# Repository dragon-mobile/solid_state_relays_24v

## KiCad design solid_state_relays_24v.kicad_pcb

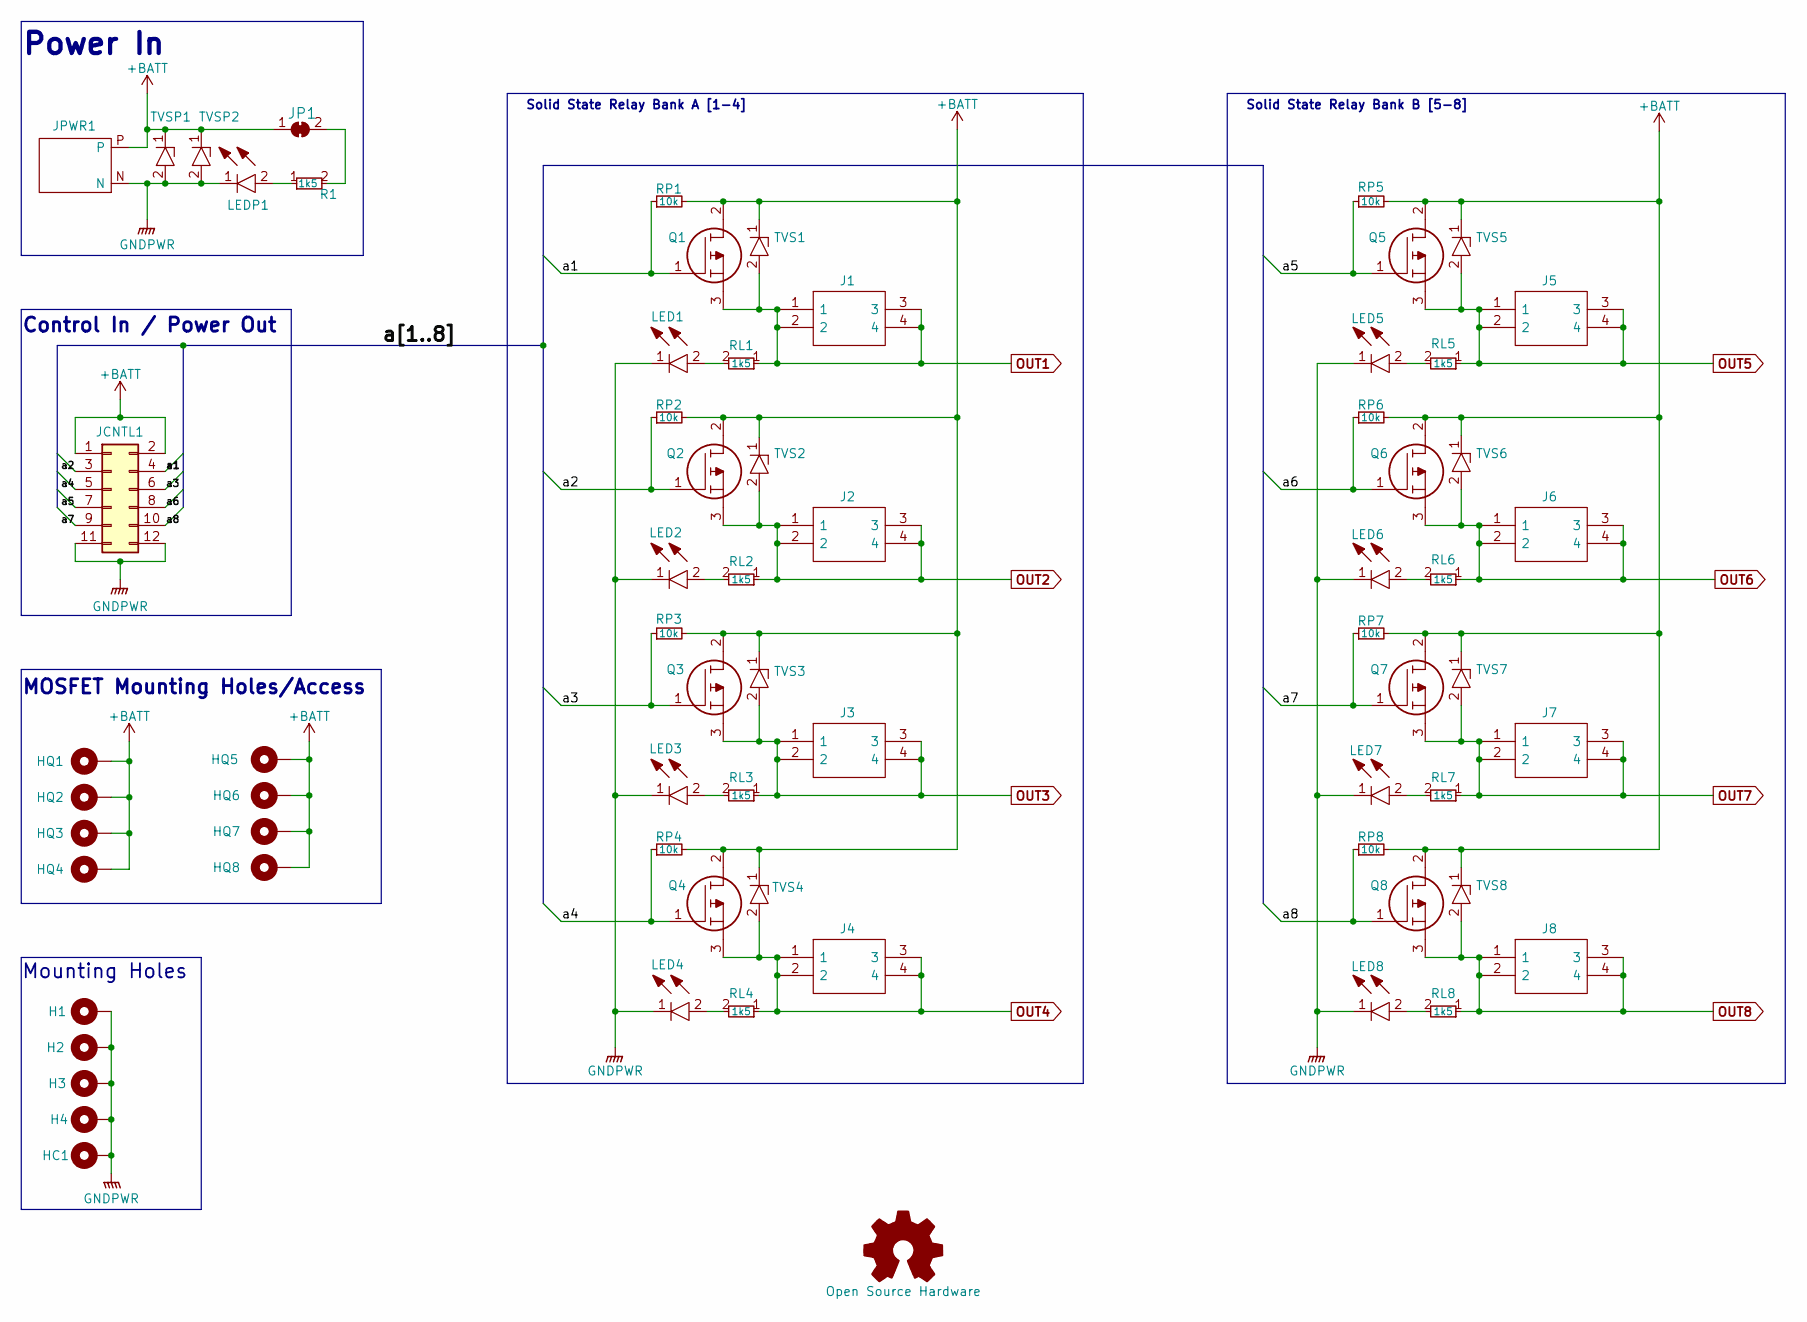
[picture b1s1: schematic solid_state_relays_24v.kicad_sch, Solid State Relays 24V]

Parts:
H1, H2, H3, H4: MountingHole; MountingHole_3.2mm_M3_Pad_Via
HC1: MountingHole; MountingHole_3.2mm_M3_Pad_Via
HQ1, HQ2, HQ3, HQ4, HQ5, HQ6, HQ7, HQ8: HeatsinkHole; MountingHole_3.2mm_M3_Pad_Via
J1, J2, J3, J4, J5, J6, J7, J8: 1190297; Mouser Part Number 651-1190297
JCNTL1: Conn_02x06_Odd_Even; IDC-Header_2x06_P2.54mm_Horizontal; MPN 78207-1012HLF; Mouser Part Number 649-78207-112HLF
JP1: SolderJumper_2_Bridged; SolderJumper-2_P1.3mm_Bridged_RoundedPad1.0x1.5mm
JPWR1: XT60PW-M; XT60PWM; Manufacturer_Part_Number XT60PW-M
LED1, LED2, LED3, LED4, LED5, LED6, LED7, LED8: LTST-C190KFKT; LEDC1607X80N; Mouser Part Number 859-LTST-C190KFKT
LEDP1: LTST-C190KGKT; LEDC1608X80N; Mouser Part Number 859-LTST-C190KGKT
Q1, Q2, Q3, Q4, Q5, Q6, Q7, Q8: IRF4905PBF; TO254P469X1042X1967-3P; Mouser Part Number 942-IRF4905PBF
R1: 1k5; RESC2012X65N; Manufacturer_Part_Number SDR10EZPJ152; Mouser Part Number 755-SDR10EZPJ152
RL1, RL2, RL3, RL4, RL5, RL6, RL7, RL8: 1k5; RESC2012X65N; Manufacturer_Part_Number SDR10EZPJ152; Mouser Part Number 755-SDR10EZPJ152
RP1, RP2, RP3, RP4, RP5, RP6, RP7, RP8: 10k; RESC2012X65N
TVS1, TVS2, TVS3, TVS4, TVS5, TVS6, TVS7, TVS8: SM6T30AY; SMBJ36CATR; Mouser Part Number 511-SM6T30AY
TVSP1, TVSP2: SM6T30AY; SMBJ36CATR; Mouser Part Number 511-SM6T30AY

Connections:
+BATT: HQ1.1, HQ2.1, HQ3.1, HQ4.1, HQ5.1, HQ6.1, HQ7.1, HQ8.1, JCNTL1.1, JCNTL1.2, JP1.1 (A), JPWR1.P, Q1.2, Q2.2, Q3.2, Q4.2, Q5.2, Q6.2, Q7.2, Q8.2, RP1.2, RP2.2, RP3.2, RP4.2, RP5.2, RP6.2, RP7.2, RP8.2, TVS1.1, TVS2.1, TVS3.1, TVS4.1, TVS5.1, TVS6.1, TVS7.1, TVS8.1, TVSP1.1, TVSP2.1
/a1: JCNTL1.4, Q1.1, RP1.1
/a2: JCNTL1.3, Q2.1, RP2.1
/a3: JCNTL1.6, Q3.1, RP3.1
/a4: JCNTL1.5, Q4.1, RP4.1
/a5: JCNTL1.7, Q5.1, RP5.1
/a6: JCNTL1.8, Q6.1, RP6.1
/a7: JCNTL1.9, Q7.1, RP7.1
/a8: JCNTL1.10, Q8.1, RP8.1
GNDPWR: H1.1, H2.1, H3.1, H4.1, HC1.1, JCNTL1.11, JCNTL1.12, JPWR1.N, LED1.1, LED2.1, LED3.1, LED4.1, LED5.1, LED6.1, LED7.1, LED8.1, LEDP1.1, TVSP1.2, TVSP2.2
unnamed: JP1.2 (B), R1.2
unnamed: LED1.2, RL1.2
unnamed: LED2.2, RL2.2
unnamed: LED3.2, RL3.2
unnamed: LED4.2, RL4.2
unnamed: LED5.2, RL5.2
unnamed: LED6.2, RL6.2
unnamed: LED7.2, RL7.2
unnamed: LED8.2, RL8.2
unnamed: LEDP1.2, R1.1
OUT1: J1.1, J1.2, J1.3, J1.4, Q1.3, RL1.1, TVS1.2
OUT2: J2.1, J2.2, J2.3, J2.4, Q2.3, RL2.1, TVS2.2
OUT3: J3.1, J3.2, J3.3, J3.4, Q3.3, RL3.1, TVS3.2
OUT4: J4.1, J4.2, J4.3, J4.4, Q4.3, RL4.1, TVS4.2
OUT5: J5.1, J5.2, J5.3, J5.4, Q5.3, RL5.1, TVS5.2
OUT6: J6.1, J6.2, J6.3, J6.4, Q6.3, RL6.1, TVS6.2
OUT7: J7.1, J7.2, J7.3, J7.4, Q7.3, RL7.1, TVS7.2
OUT8: J8.1, J8.2, J8.3, J8.4, Q8.3, RL8.1, TVS8.2

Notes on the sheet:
Control In / Power Out
Mounting Holes
MOSFET Mounting Holes/Access
Solid State Relay Bank B [5-8]
Solid State Relay Bank A [1-4]
Power In

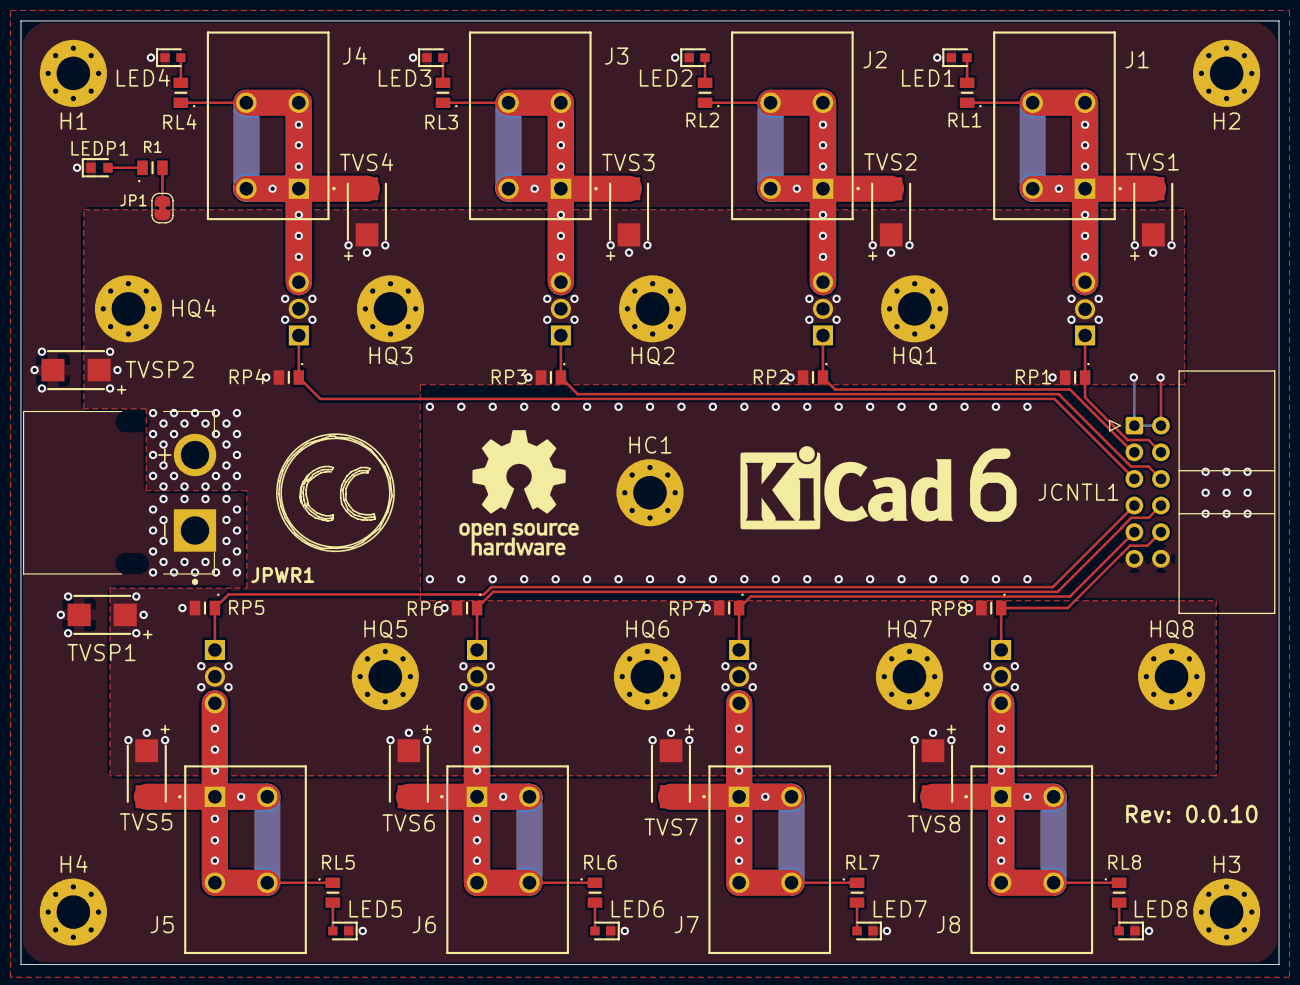
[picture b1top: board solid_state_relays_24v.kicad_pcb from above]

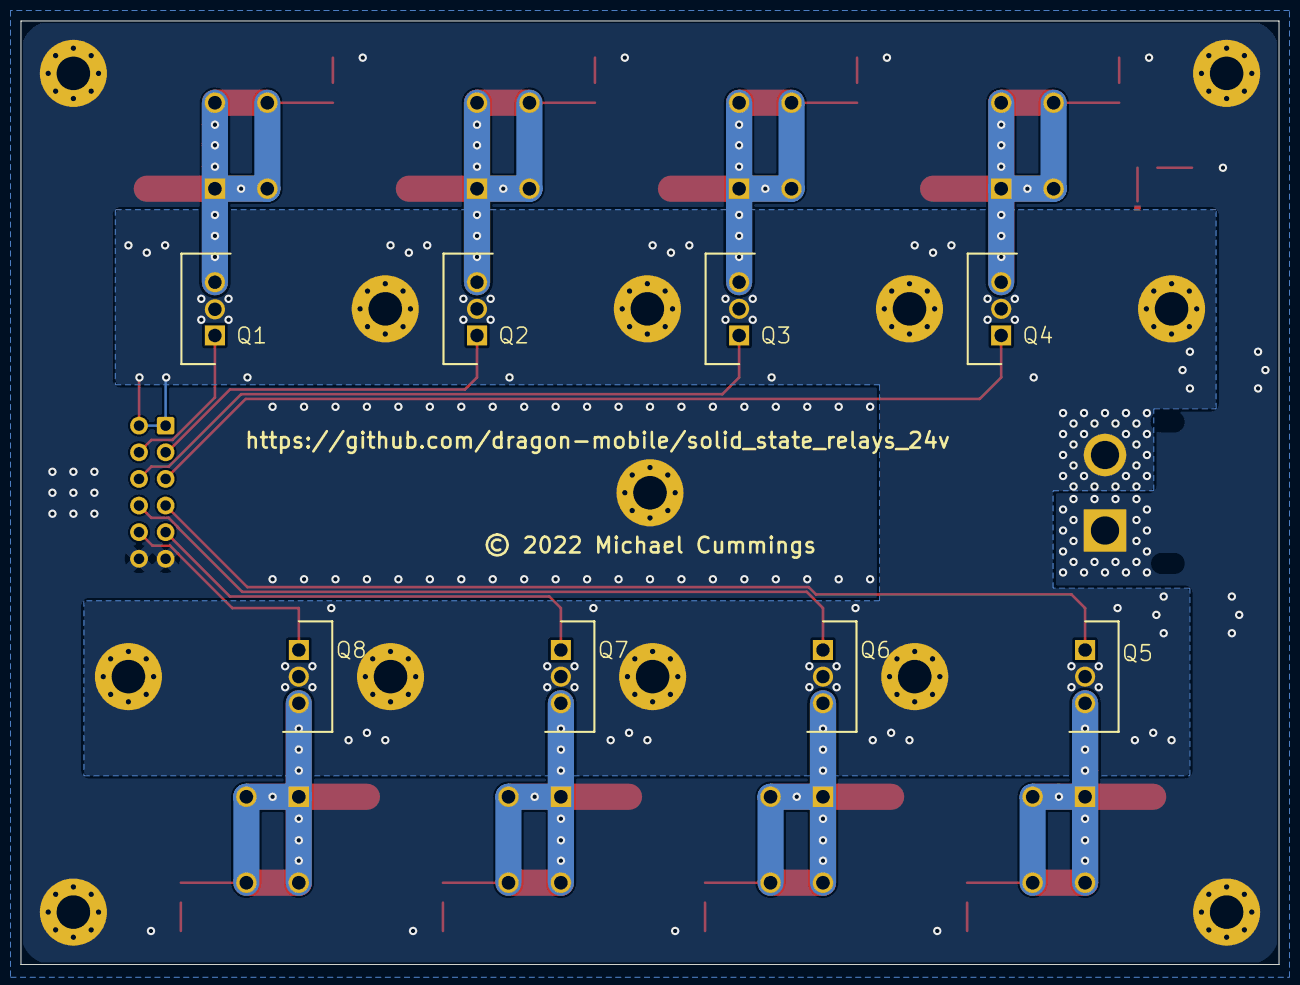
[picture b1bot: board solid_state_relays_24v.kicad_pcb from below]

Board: 2 copper layers, 120.0 x 90.0 mm, 68 parts (8 on the bottom side), 28 nets.

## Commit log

2022-06-25 Added gitignore
2022-06-25 Ignoring kicad_prl
2022-06-25 Updating gitignore
2022-06-26 Increased text size on PCB and updated to v0.0.6
2022-06-26 Admin updates to v0.0.6
2022-06-26 Added gerber and drill files
2022-06-30 Total redo on schematic for v0.0.8
2022-07-01 Updating schematic and PCB for v0.0.8
2022-07-13 v0.0.10-pre1
2022-07-14 v0.0.10-pre2

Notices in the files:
solid_state_relays_24v.kicad_pcb:
creativecommons.org/licenses/by/4.0
License: CC By 4.0
© 2022 Michael Cummings
